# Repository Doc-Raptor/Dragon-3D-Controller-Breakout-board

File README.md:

# Dragon-3D-Controller-Breakout-board
A board for use as a base for 3D printer controller board.
Can be used for up to 36V in theory

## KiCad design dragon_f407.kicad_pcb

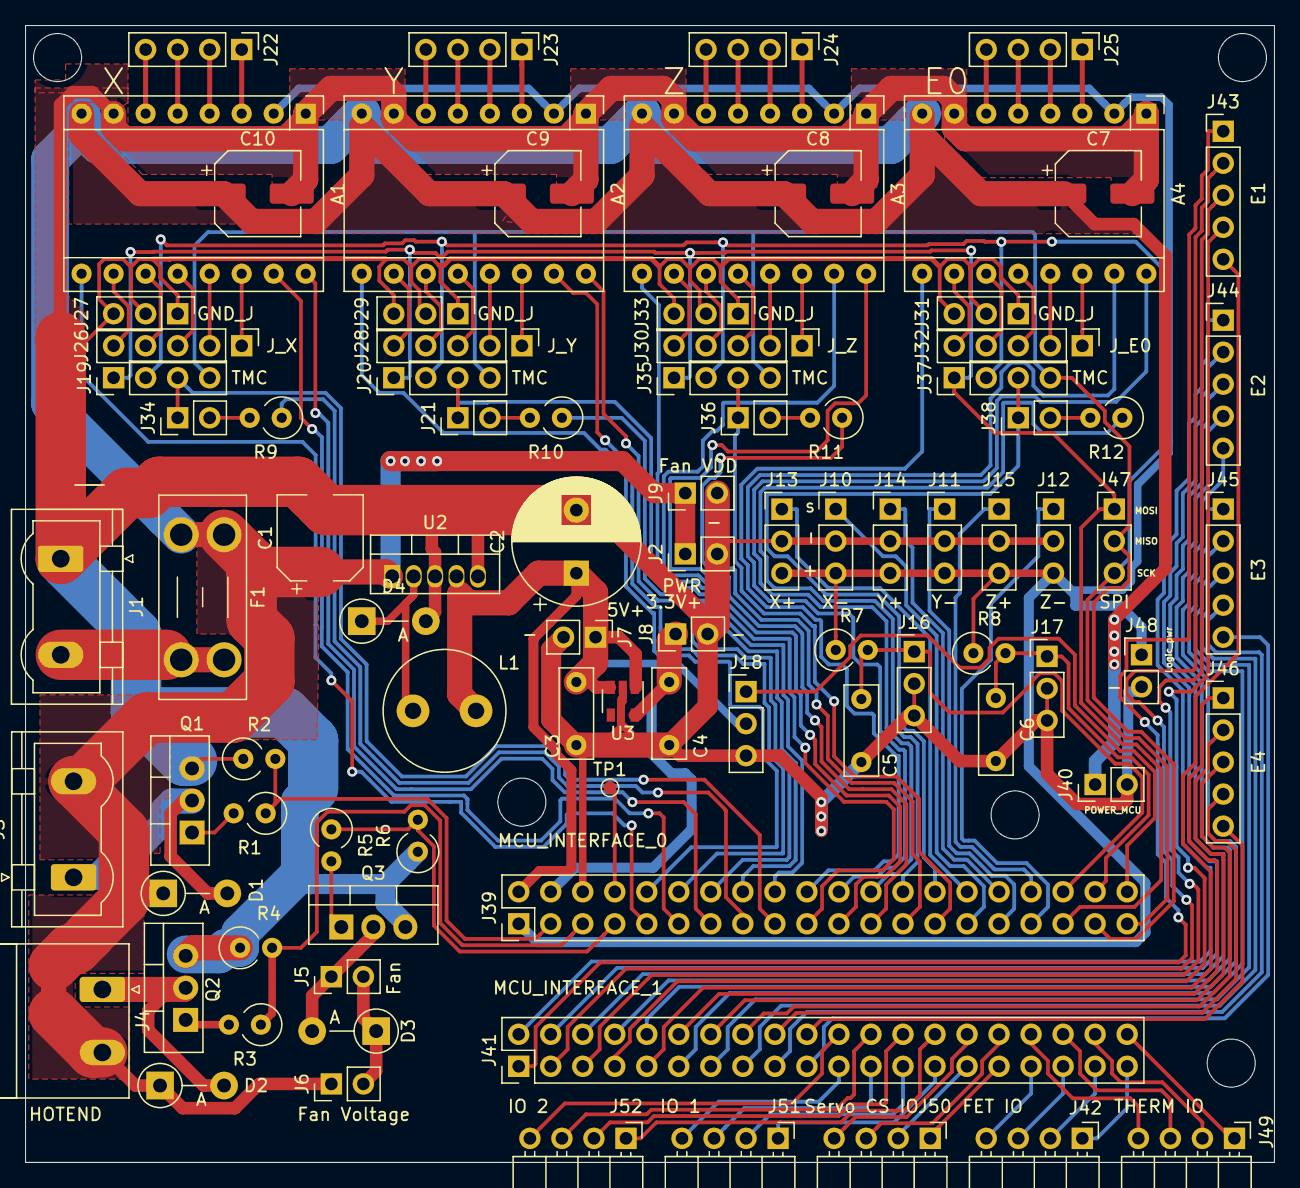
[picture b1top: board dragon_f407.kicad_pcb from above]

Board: 2 copper layers, 99.1 x 90.2 mm, 90 parts (0 on the bottom side), 130 nets.

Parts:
A1, A2, A3, A4: Pololu_Breakout_A4988; Pololu_Breakout-16_15.2x20.3mm
C1, C7, C8, C9, C10: 100uF; CP_Elec_6.3x7.7
C2: 330uF; CP_Radial_D10.0mm_P5.00mm
C3, C4: 1uF; C_Disc_D7.0mm_W2.5mm_P5.00mm
C5, C6: 10uF; C_Disc_D7.0mm_W2.5mm_P5.00mm
D1, D2, D3, D4: 1N5819; D_DO-41_SOD81_P5.08mm_Vertical_AnodeUp
F1: Fuse; Fuseholder_Blade_Mini_Keystone_3568
J1: POWER_IN; PhoenixContact_GMSTBVA_2,5_2-G-7,62_1x02_P7.62mm_Vertical
J2: POWER_OUT; PinHeader_1x02_P2.54mm_Vertical
J3: HEATBED; PhoenixContact_GMSTBVA_2,5_2-G-7,62_1x02_P7.62mm_Vertical
J4: HOTEND; PhoenixContact_MSTBA_2,5_2-G_1x02_P5.00mm_Horizontal
J5: FAN; PinHeader_1x02_P2.54mm_Vertical
J6: FAN_VOLTAGE; PinHeader_1x02_P2.54mm_Vertical
J7: 5V; PinHeader_1x02_P2.54mm_Vertical
J8: 3.3V; PinHeader_1x02_P2.54mm_Vertical
J9: FAN_VDD; PinHeader_1x02_P2.54mm_Vertical
J10: X-; PinHeader_1x03_P2.54mm_Vertical
J11: Y-; PinHeader_1x03_P2.54mm_Vertical
J12: Z-; PinHeader_1x03_P2.54mm_Vertical
J13: X+; PinHeader_1x03_P2.54mm_Vertical
J14: Y+; PinHeader_1x03_P2.54mm_Vertical
J15: Z+; PinHeader_1x03_P2.54mm_Vertical
J16: T_BED; PinHeader_1x03_P2.54mm_Vertical
J17: T_E0; PinHeader_1x03_P2.54mm_Vertical
J18: SERVO; PinHeader_1x03_P2.54mm_Vertical
J19: X_TMC; PinHeader_1x04_P2.54mm_Vertical
J20: Y_TMC; PinHeader_1x04_P2.54mm_Vertical
J21: UART_Y; PinHeader_1x02_P2.54mm_Vertical
J22: X_STEPPER; PinHeader_1x04_P2.54mm_Vertical
J23: Y_STEPPER; PinHeader_1x04_P2.54mm_Vertical
J24: Z_STEPPER; PinHeader_1x04_P2.54mm_Vertical
J25: E0_STEPPER; PinHeader_1x04_P2.54mm_Vertical
J26: X_PINS; PinHeader_1x05_P2.54mm_Vertical
J27: X_GND; PinHeader_1x03_P2.54mm_Vertical
J28: Y_PINS; PinHeader_1x05_P2.54mm_Vertical
J29: Y_GND; PinHeader_1x03_P2.54mm_Vertical
J30: Z_PINS; PinHeader_1x05_P2.54mm_Vertical
J31: Z_GND; PinHeader_1x03_P2.54mm_Vertical
J32: E0_PINS; PinHeader_1x05_P2.54mm_Vertical
J33: E0_GND; PinHeader_1x03_P2.54mm_Vertical
J34: UART_X; PinHeader_1x02_P2.54mm_Vertical
J35: Z_TMC; PinHeader_1x04_P2.54mm_Vertical
J36: UART_Z; PinHeader_1x02_P2.54mm_Vertical
J37: E0_TMC; PinHeader_1x04_P2.54mm_Vertical
J38: UART_E0; PinHeader_1x02_P2.54mm_Vertical
J39: MCU_Interface_0; PinHeader_2x20_P2.54mm_Vertical
J40: POWER; PinHeader_1x02_P2.54mm_Vertical
J41: MCU_Interface_1; PinHeader_2x20_P2.54mm_Vertical
J42: FET_IO; PinHeader_1x04_P2.54mm_Horizontal
J43: E1; PinHeader_1x05_P2.54mm_Vertical
J44: E2; PinHeader_1x05_P2.54mm_Vertical
J45: E3; PinHeader_1x05_P2.54mm_Vertical
J46: E4; PinHeader_1x05_P2.54mm_Vertical
J47: SPI; PinHeader_1x03_P2.54mm_Vertical
J48: Logic_PWR; PinHeader_1x02_P2.54mm_Vertical
J49: T_IO; PinHeader_1x04_P2.54mm_Horizontal
J50: SV_CS_IO; PinHeader_1x04_P2.54mm_Horizontal
J51: IO_1; PinHeader_1x04_P2.54mm_Horizontal
J52: IO_2; PinHeader_1x04_P2.54mm_Horizontal
L1: 330uhH; L_Radial_D9.5mm_P5.00mm_Fastron_07HVP
Q1, Q2, Q3: IRF3205; TO-220-3_Vertical
R1, R3: 100; R_Axial_DIN0309_L9.0mm_D3.2mm_P2.54mm_Vertical
R2, R4, R7, R8: 4K7; R_Axial_DIN0309_L9.0mm_D3.2mm_P2.54mm_Vertical
R5, R9, R10, R11, R12: 1K; R_Axial_DIN0309_L9.0mm_D3.2mm_P2.54mm_Vertical
R6: 10K; R_Axial_DIN0309_L9.0mm_D3.2mm_P2.54mm_Vertical
TP1: RESET; TestPoint_Pad_D1.0mm
U2: LM2575-5.0BT; TO-220-5_Vertical
U3: RT9013-33GB; SOT-23-5

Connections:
+3V3: C4.1, J8.1, J39.4, U3.5
+5V: C2.1, C3.1, J7.1, J18.2, J39.2, L1.2, U2.4, U3.1, U3.3
CS0: J41.30, J50.4
CS1: J41.32, J50.3
CS_RX_E0: J37.3, J38.1, J39.28
CS_RX_E1: J41.9, J43.5
CS_RX_E2: J41.10, J44.5
CS_RX_E3: J41.19, J45.5
CS_RX_E4: J41.20, J46.5
CS_RX_X: J19.3, J34.1, J39.17
CS_RX_Y: J20.3, J21.1, J39.18
CS_RX_Z: J35.3, J36.1, J39.27
DIR_E0: A4.16, J39.24
DIR_E1: J41.5, J43.3
DIR_E2: J41.6, J44.3
DIR_E3: J41.15, J45.3
DIR_E4: J41.16, J46.3
DIR_X: A1.16, J39.13
DIR_Y: A2.16, J39.14
DIR_Z: A3.16, J39.23
EN_E0: A4.9, J39.20
EN_E1: J41.1, J43.1
EN_E2: J41.2, J44.1
EN_E3: J41.11, J45.1
EN_E4: J41.12, J46.1
EN_X: A1.9, J39.9
EN_Y: A2.9, J39.10
EN_Z: A3.9, J39.19
FET1: J39.3, R1.1, R2.2
FET2: J39.5, R3.1, R4.2
FET3: J39.7, R5.1, R6.2
FET4: J41.33, J42.4
FET5: J41.35, J42.3
FET6: J41.37, J42.2
FET7: J41.39, J42.1
GND: A1.1, A1.7, A2.1, A2.7, A3.1, A3.7, A4.1, A4.7, C1.2, C2.2, C3.2, C4.2, C5.1, C6.2, C7.2, C8.2, C9.2, C10.2, D4.2, J1.1, J2.2, J7.2, J8.2, J9.2, J10.2, J11.2, J12.2, J13.2, J14.2, J15.2, J16.2, J16.3, J17.2, J17.3, J18.3, J27.1, J27.2, J27.3, J29.1, J29.2, J29.3, J31.1, J31.2, J31.3, J33.1, J33.2, J33.3, J39.6, J40.2, J48.2, Q1.3, Q2.3, Q3.3, R2.1, R4.1, R6.1, U2.3, U2.5, U3.2
IO0: J41.21, J51.4
IO1: J41.23, J51.3
IO2: J41.25, J51.2
IO3: J41.27, J51.1
IO4: J41.22, J52.4
IO5: J41.24, J52.3
IO6: J41.26, J52.2
IO7: J41.28, J52.1
Logic_PWR: A1.2, A2.2, A3.2, A4.2, J10.3, J11.3, J12.3, J13.3, J14.3, J15.3, J39.1, J48.1, R7.1, R8.1
MISO: J19.4, J20.4, J35.4, J37.4, J39.37, J47.2
MOSI: J19.1, J20.1, J35.1, J37.1, J39.35, J47.1
unnamed: A1.3, J22.1
unnamed: A1.4, J22.2
unnamed: A1.5, J22.3
unnamed: A1.6, J22.4
unnamed: A1.10, J26.5
unnamed: A1.11, J26.4
unnamed: A1.12, J26.3
unnamed: A1.13, J26.2
unnamed: A1.14, J26.1
unnamed: A2.3, J23.1
unnamed: A2.4, J23.2
unnamed: A2.5, J23.3
unnamed: A2.6, J23.4
unnamed: A2.10, J28.5
unnamed: A2.11, J28.4
unnamed: A2.12, J28.3
unnamed: A2.13, J28.2
unnamed: A2.14, J28.1
unnamed: A3.3, J24.1
unnamed: A3.4, J24.2
unnamed: A3.5, J24.3
unnamed: A3.6, J24.4
unnamed: A3.10, J30.5
unnamed: A3.11, J30.4
unnamed: A3.12, J30.3
unnamed: A3.13, J30.2
unnamed: A3.14, J30.1
unnamed: A4.3, J25.1
unnamed: A4.4, J25.2
unnamed: A4.5, J25.3
unnamed: A4.6, J25.4
unnamed: A4.10, J32.5
unnamed: A4.11, J32.4
unnamed: A4.12, J32.3
unnamed: A4.13, J32.2
unnamed: A4.14, J32.1
unnamed: D1.2, J3.1, Q1.2
unnamed: D2.2, J4.1, Q2.2
unnamed: D3.1, J5.2, J6.2
unnamed: D3.2, J5.1, Q3.2
unnamed: D4.1, L1.1, U2.2
unnamed: F1.2, J1.2
unnamed: J21.2, R10.2
unnamed: J34.2, R9.2
unnamed: J36.2, R11.2
unnamed: J38.2, R12.2
unnamed: Q1.1, R1.2
unnamed: Q2.1, R3.2
unnamed: Q3.1, R5.2
RESET: J39.8, TP1.1
SCK: J19.2, J20.2, J35.2, J37.2, J39.39, J47.3
STEP_E0: A4.15, J39.22
STEP_E1: J41.3, J43.2
STEP_E2: J41.4, J44.2
STEP_E3: J41.13, J45.2
STEP_E4: J41.14, J46.2
STEP_X: A1.15, J39.11
STEP_Y: A2.15, J39.12
STEP_Z: A3.15, J39.21
SV0: J18.1, J39.40
SV1: J41.29, J50.2
SV2: J41.31, J50.1
T0: C5.2, J16.1, J39.36, R7.2
T1: C6.1, J17.1, J39.38, R8.2
T2: J41.34, J49.4
T3: J41.36, J49.3
T4: J41.38, J49.2
T5: J41.40, J49.1
TX_E0: J39.26, R12.1
TX_E1: J41.7, J43.4
TX_E2: J41.8, J44.4
TX_E3: J41.17, J45.4
TX_E4: J41.18, J46.4
TX_X: J39.15, R9.1
TX_Y: J39.16, R10.1
TX_Z: J39.25, R11.1
VDD: A1.8, A2.8, A3.8, A4.8, C1.1, C7.1, C8.1, C9.1, C10.1, D1.1, D2.1, F1.1, J2.1, J3.2, J4.2, J6.1, J9.1, J40.1, U2.1
X-MAX: J13.1, J39.30
X-MIN: J10.1, J39.29
Y-MAX: J14.1, J39.32
Y-MIN: J11.1, J39.31
Z-MAX: J15.1, J39.34
Z-MIN: J12.1, J39.33

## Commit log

2021-01-12 Fixed errors
